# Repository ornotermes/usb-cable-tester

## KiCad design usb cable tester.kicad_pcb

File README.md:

# USB Cable Tester

A simple USB cable tester that supports most cables.
It will not check for shorts, only if a wire conducts.

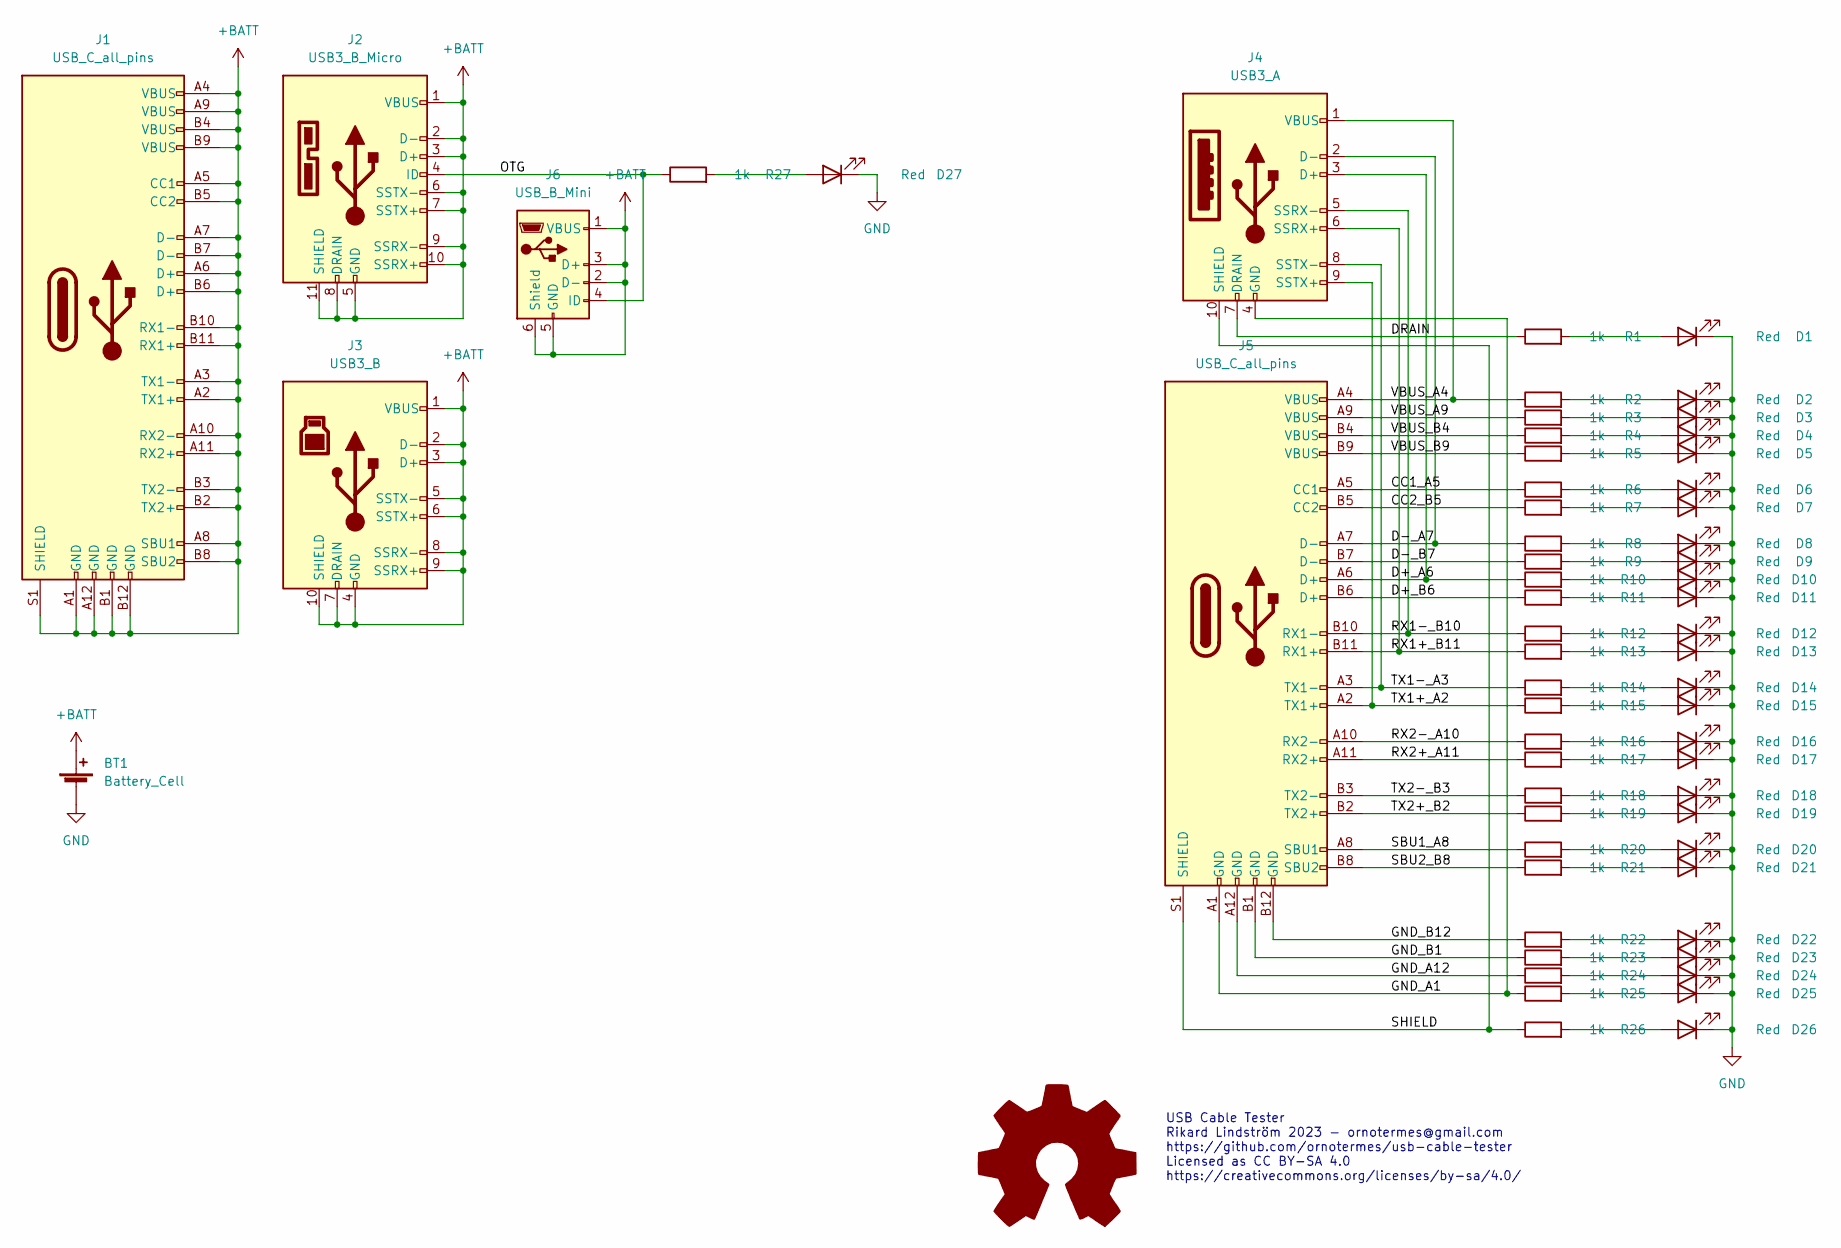
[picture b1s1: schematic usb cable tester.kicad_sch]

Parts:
BT1: Battery_Cell; BATT CR2032; MPN C2902340
D1: Red; LED_0805_2012Metric; MPN C965812
D2, D3, D4, D5, D6, D7, D8, D9, D10, D11, D12, D13, D14, D15, D16, D17, D18, D19, D20, D21, D22, D23, D24, D25, D26, D27: Red; LED_0805_2012Metric
J1, J5: USB_C_all_pins; USB-C; MPN C134092
J2: USB3_B_Micro; USB Micro-AB 3.0; MPN C464578
J3: USB3_B; USB-B 3.0; MPN C2895032
J4: USB3_A; USB-A 3.0; MPN C381140
J6: USB_B_Mini; USB Mini-AB; MPN C505287
R1: 1k; R_0805_2012Metric; MPN C2907295
R2, R3, R4, R5, R6, R7, R8, R9, R10, R11, R12, R13, R14, R15, R16, R17, R18, R19, R20, R21, R22, R23, R24, R25, R26, R27: 1k; R_0805_2012Metric

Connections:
+BATT: BT1.1 (+), J1.A1 (GND), J1.A2 (TX1+), J1.A3 (TX1-), J1.A4 (VBUS), J1.A5 (CC1), J1.A6 (D+), J1.A7 (D-), J1.A8 (SBU1), J1.A9 (VBUS), J1.A10 (RX2-), J1.A11 (RX2+), J1.A12 (GND), J1.B1 (GND), J1.B2 (TX2+), J1.B3 (TX2-), J1.B4 (VBUS), J1.B5 (CC2), J1.B6 (D+), J1.B7 (D-), J1.B8 (SBU2), J1.B9 (VBUS), J1.B10 (RX1-), J1.B11 (RX1+), J1.B12 (GND), J1.S1 (SHIELD), J2.1 (VBUS), J2.2 (D-), J2.3 (D+), J2.5 (GND), J2.6 (SSTX-), J2.7 (SSTX+), J2.8 (DRAIN), J2.9 (SSRX-), J2.10 (SSRX+), J2.11 (SHIELD), J3.1 (VBUS), J3.2 (D-), J3.3 (D+), J3.4 (GND), J3.5 (SSTX-), J3.6 (SSTX+), J3.7 (DRAIN), J3.8 (SSRX-), J3.9 (SSRX+), J3.10 (SHIELD), J6.1 (VBUS), J6.2 (D-), J6.3 (D+), J6.5 (GND), J6.6 (Shield)
/CC1_A5: J5.A5 (CC1), R6.1
/CC2_B5: J5.B5 (CC2), R7.1
/D+_A6: J4.3 (D+), J5.A6 (D+), R10.1
/D+_B6: J5.B6 (D+), R11.1
/D-_A7: J4.2 (D-), J5.A7 (D-), R8.1
/D-_B7: J5.B7 (D-), R9.1
/DRAIN: J4.7 (DRAIN), R1.1
/GND_A1: J4.4 (GND), J5.A1 (GND), R25.1
/GND_A12: J5.A12 (GND), R24.1
/GND_B1: J5.B1 (GND), R23.1
/GND_B12: J5.B12 (GND), R22.1
/OTG: J2.4 (ID), J6.4 (ID), R27.1
/RX1+_B11: J4.6 (SSRX+), J5.B11 (RX1+), R13.1
/RX1-_B10: J4.5 (SSRX-), J5.B10 (RX1-), R12.1
/RX2+_A11: J5.A11 (RX2+), R17.1
/RX2-_A10: J5.A10 (RX2-), R16.1
/SBU1_A8: J5.A8 (SBU1), R20.1
/SBU2_B8: J5.B8 (SBU2), R21.1
/SHIELD: J4.10 (SHIELD), J5.S1 (SHIELD), R26.1
/TX1+_A2: J4.9 (SSTX+), J5.A2 (TX1+), R15.1
/TX1-_A3: J4.8 (SSTX-), J5.A3 (TX1-), R14.1
/TX2+_B2: J5.B2 (TX2+), R19.1
/TX2-_B3: J5.B3 (TX2-), R18.1
/VBUS_A4: J4.1 (VBUS), J5.A4 (VBUS), R2.1
/VBUS_A9: J5.A9 (VBUS), R3.1
/VBUS_B4: J5.B4 (VBUS), R4.1
/VBUS_B9: J5.B9 (VBUS), R5.1
GND: BT1.2 (-), D1.1 (K), D2.1 (K), D3.1 (K), D4.1 (K), D5.1 (K), D6.1 (K), D7.1 (K), D8.1 (K), D9.1 (K), D10.1 (K), D11.1 (K), D12.1 (K), D13.1 (K), D14.1 (K), D15.1 (K), D16.1 (K), D17.1 (K), D18.1 (K), D19.1 (K), D20.1 (K), D21.1 (K), D22.1 (K), D23.1 (K), D24.1 (K), D25.1 (K), D26.1 (K), D27.1 (K)
unnamed: D1.2 (A), R1.2
unnamed: D2.2 (A), R2.2
unnamed: D3.2 (A), R3.2
unnamed: D4.2 (A), R4.2
unnamed: D5.2 (A), R5.2
unnamed: D6.2 (A), R6.2
unnamed: D7.2 (A), R7.2
unnamed: D8.2 (A), R8.2
unnamed: D9.2 (A), R9.2
unnamed: D10.2 (A), R10.2
unnamed: D11.2 (A), R11.2
unnamed: D12.2 (A), R12.2
unnamed: D13.2 (A), R13.2
unnamed: D14.2 (A), R14.2
unnamed: D15.2 (A), R15.2
unnamed: D16.2 (A), R16.2
unnamed: D17.2 (A), R17.2
unnamed: D18.2 (A), R18.2
unnamed: D19.2 (A), R19.2
unnamed: D20.2 (A), R20.2
unnamed: D21.2 (A), R21.2
unnamed: D22.2 (A), R22.2
unnamed: D23.2 (A), R23.2
unnamed: D24.2 (A), R24.2
unnamed: D25.2 (A), R25.2
unnamed: D26.2 (A), R26.2
unnamed: D27.2 (A), R27.2

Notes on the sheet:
USB Cable Tester Rikard Lindström 2023 - ornotermes@gmail.com https://github.com/ornotermes/usb-cable-tester Licensed as CC BY-SA 4.0 https://creativecommons.org/licenses/by-sa/4.0/

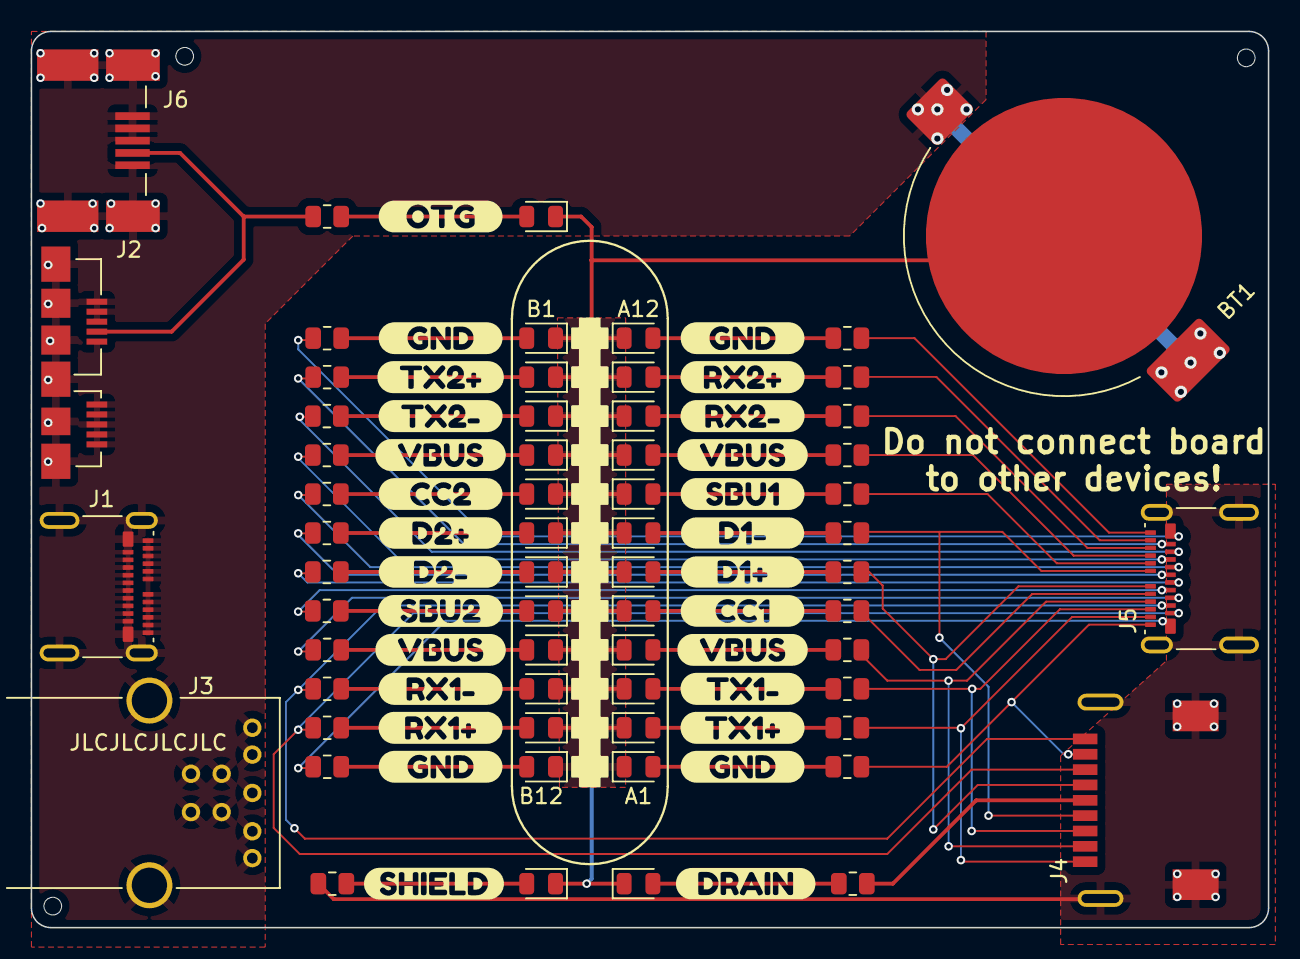
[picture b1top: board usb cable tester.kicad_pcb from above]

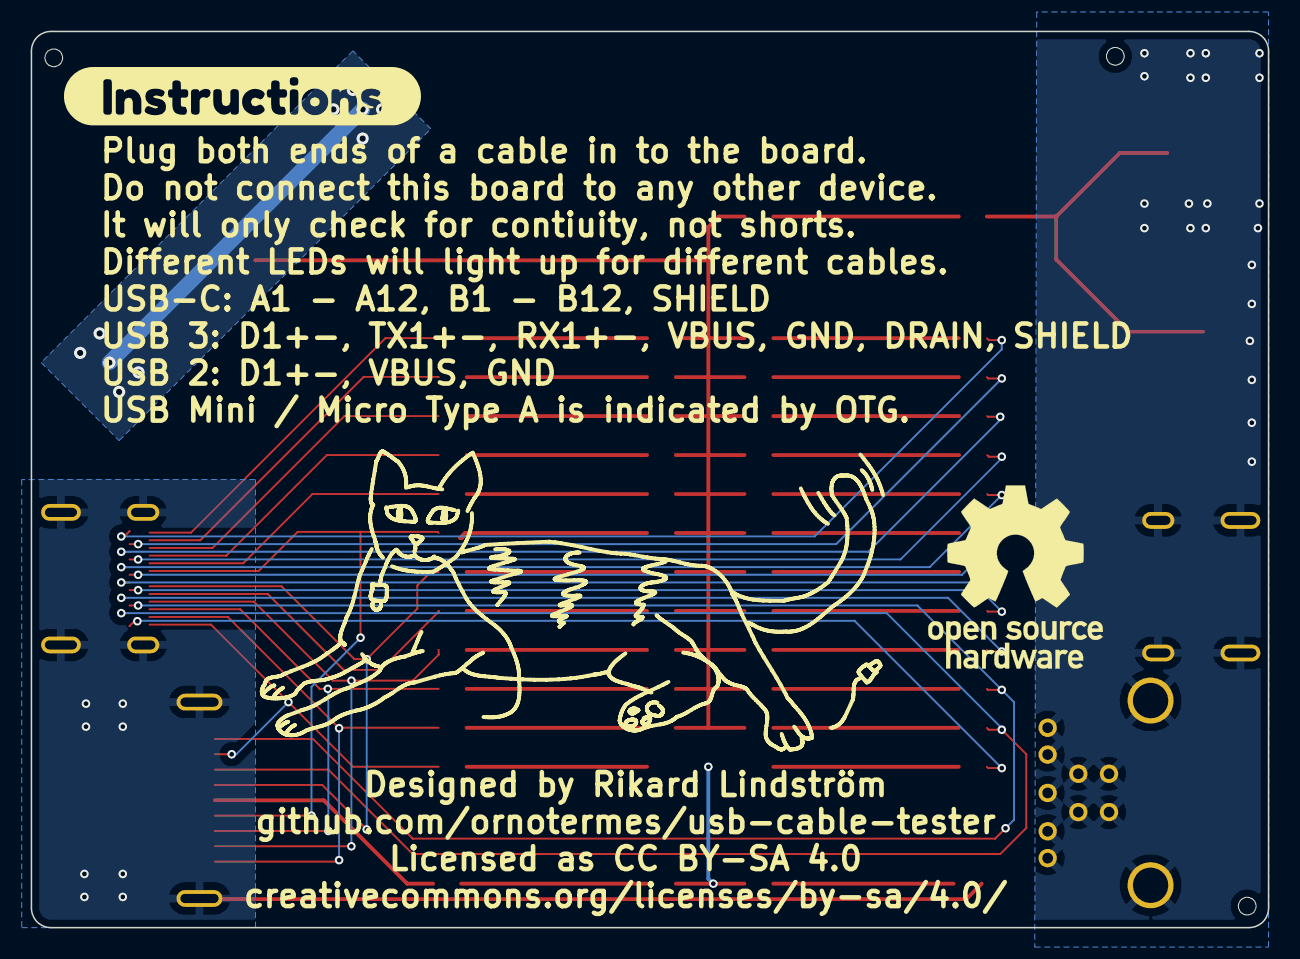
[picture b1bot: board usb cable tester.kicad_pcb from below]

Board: 2 copper layers, 80.6 x 58.4 mm, 97 parts (4 on the bottom side), 56 nets.

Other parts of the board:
SYM1: OSHW-Logo2_14.6x12mm_Mask; OSHW-Symbol_6.7x6mm_Copper
SYM2: OSHW-Logo_11.4x12mm_SilkScreen
SYM3: cat
SYM4: KiCad-Logo2_5mm_Copper; KiCad-Logo2_5mm_Mask
TOOLING1, TOOLING2, TOOLING3: Tooling Hole
kibuzzard-63BE21A2, kibuzzard-63BE21A2#2, kibuzzard-63BE21A2#3, kibuzzard-63BE21A2#4: G***; kibuzzard-63BE21A2
kibuzzard-63BE21A7: G***; kibuzzard-63BE21A7
kibuzzard-63BE21AF: G***; kibuzzard-63BE21AF
kibuzzard-63BE21B8, kibuzzard-63BE21B8#2, kibuzzard-63BE21B8#3, kibuzzard-63BE21B8#4: G***; kibuzzard-63BE21B8
kibuzzard-63BE21EC: G***; kibuzzard-63BE21EC
kibuzzard-63BE23A5: G***; kibuzzard-63BE23A5
kibuzzard-63BE23B1: G***; kibuzzard-63BE23B1
kibuzzard-63BE23BC: G***; kibuzzard-63BE23BC
kibuzzard-63BE24BE: G***; kibuzzard-63BE24BE
kibuzzard-63BE228F: G***; kibuzzard-63BE228F
kibuzzard-63BE2235: G***; kibuzzard-63BE2235
kibuzzard-63BE2283: G***; kibuzzard-63BE2283
kibuzzard-63BE2364: G***; kibuzzard-63BE2364
kibuzzard-63BE2390: G***; kibuzzard-63BE2390
kibuzzard-63BE2399: G***; kibuzzard-63BE2399
kibuzzard-63BE2450: G***; kibuzzard-63BE2450
kibuzzard-63C31A6A: G***; kibuzzard-63C31A6A
kibuzzard-63C31A8C: G***; kibuzzard-63C31A8C
kibuzzard-63C31A73: G***; kibuzzard-63C31A73
kibuzzard-63C31A82: G***; kibuzzard-63C31A82
kibuzzard-63C319E2: G***; kibuzzard-63C319E2
kibuzzard-63C341AF: G***; kibuzzard-63C341AF
kibuzzard-63C37626: G***; kibuzzard-63C37626

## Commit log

2023-01-15 First!
2023-01-15 SVG of cat drawing
2023-01-15 .gitignore for KiCAD projects
2023-01-16 Initial library of custom symbols and footprints
2023-01-16 Ignore more files
2023-01-16 Project, schematic, and layout files
2023-01-16 Added a couple of images of the PCB
2023-01-16 Fixed file extention, added a bit of text + images
2023-01-18 Updated net names to make stuff more understanable
2023-01-18 Synced footprints and changed references
2023-01-18 Change values of resistors and LEDs
2023-01-18 Fix values missed before, hide some stuff from BOM
2023-01-18 Make hidden in BOM by default
2023-01-18 Added LCSC part numbers
2023-01-18 Ignore the file #auto_saved_files#
